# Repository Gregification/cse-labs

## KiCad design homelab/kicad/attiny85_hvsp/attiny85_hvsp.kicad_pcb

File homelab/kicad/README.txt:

sources & breif instructions for everything in the libraries folder
	clone the github / gitlab ones

https://github.com/Digi-Key/digikey-kicad-library
https://gitlab.com/kicad/libraries/kicad-symbols
https://gitlab.com/kicad/libraries/kicad-footprints

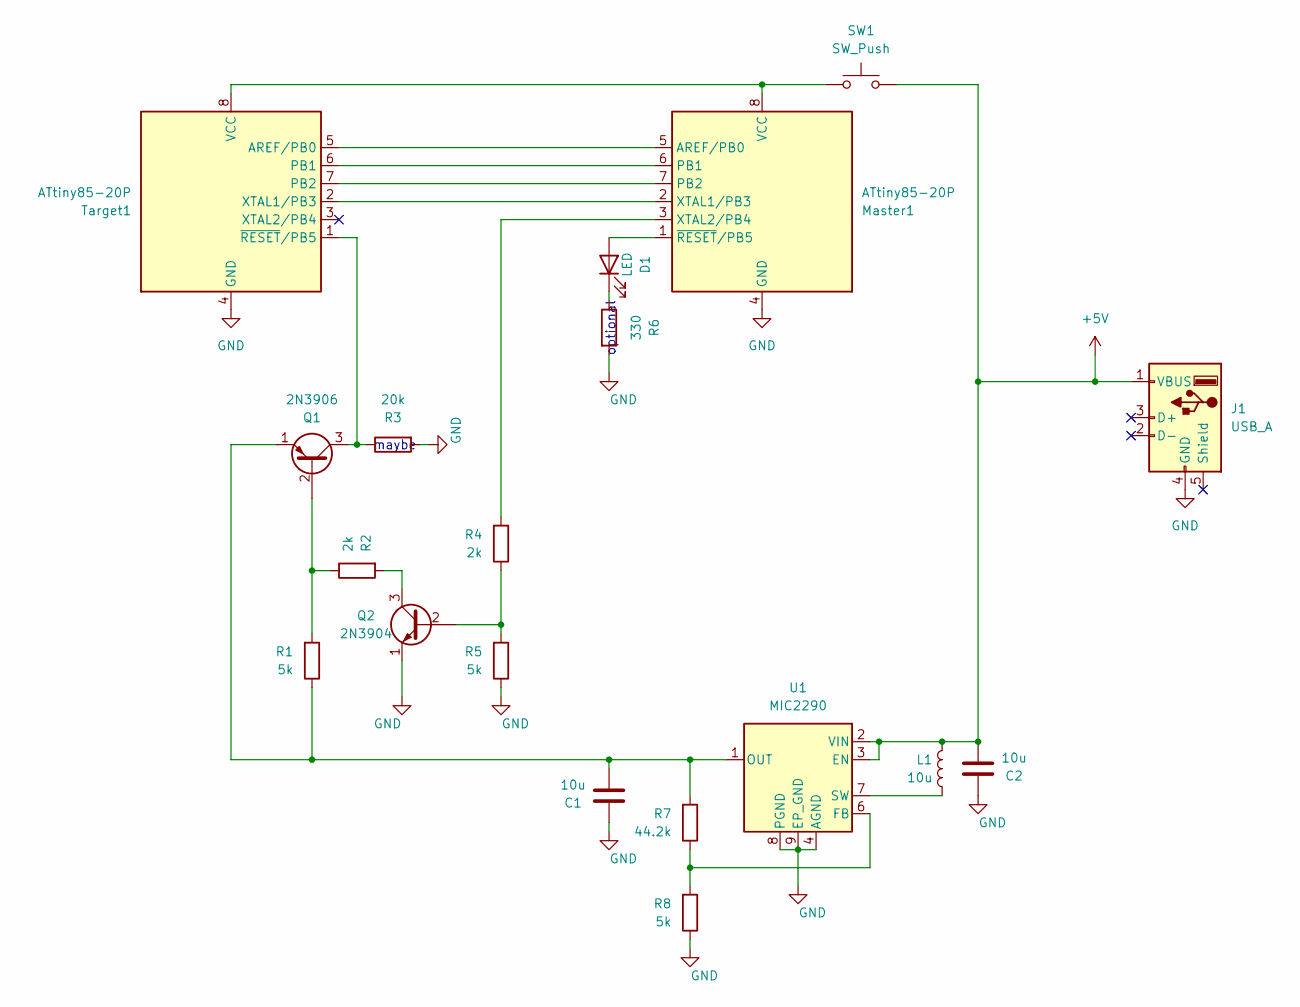
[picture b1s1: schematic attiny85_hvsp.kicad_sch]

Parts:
C1, C2: 10u; C_1210_3225Metric
D1: LED; LED_Rectangular_W3.0mm_H2.0mm
J1: USB_A; USB_A_Molex_48037-2200_Horizontal
L1: 10u; IDCP2218-01
Master1: ATtiny85-20P; DIP-8_W7.62mm
Q1: 2N3906; TO-92L_HandSolder
Q2: 2N3904; TO-92L_HandSolder
R1, R5, R8: 5k; R_0805_2012Metric
R2, R4: 2k; R_0603_1608Metric
R3: 20k; R_0805_2012Metric
R6: 330; R_2010_5025Metric
R7: 44.2k; R_1206_3216Metric
SW1: SW_Push; SW_SPST_Omron_B3FS-101xP
Target1: ATtiny85-20P; DIP-8_W7.62mm
U1: MIC2290; Micrel_MLF-8-1EP_2x2mm_P0.5mm_EP0.6x1.2mm

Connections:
+5V: C2.1, J1.1 (VBUS), L1.1, SW1.2, U1.2 (VIN), U1.3 (EN)
GND: C1.2, C2.2, J1.4 (GND), Master1.4 (GND), Q2.1 (E), R3.2, R5.1, R6.2, R8.1, Target1.4 (GND), U1.4 (AGND), U1.8 (PGND), U1.9 (EP_GND)
unnamed: D1.2 (A), Master1.1 (~RESET/PB5)
unnamed: D1.1 (K), R6.1
unnamed: Master1.5 (AREF/PB0), Target1.5 (AREF/PB0)
unnamed: Master1.6 (PB1), Target1.6 (PB1)
unnamed: Master1.7 (PB2), Target1.7 (PB2)
unnamed: Master1.8 (VCC), SW1.1, Target1.8 (VCC)
unnamed: Master1.2 (XTAL1/PB3), Target1.2 (XTAL1/PB3)
unnamed: Master1.3 (XTAL2/PB4), R4.2
unnamed: Q1.2 (B), R1.2, R2.1
unnamed: Q1.3 (C), R3.1, Target1.1 (~RESET/PB5)
unnamed: C1.1, Q1.1 (E), R1.1, R7.2, U1.1 (OUT)
unnamed: Q2.2 (B), R4.1, R5.2
unnamed: Q2.3 (C), R2.2
unnamed: R7.1, R8.2, U1.6 (FB)
unnamed: L1.2, U1.7 (SW)

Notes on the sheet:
maybe
optional

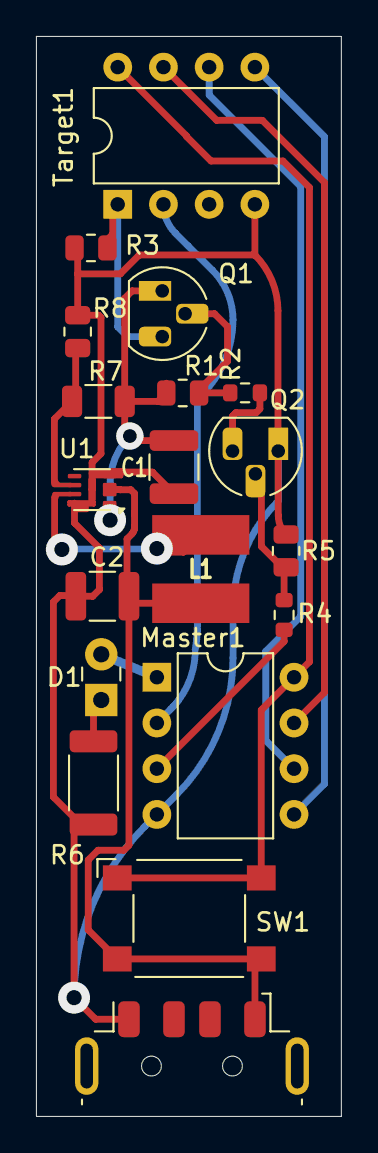
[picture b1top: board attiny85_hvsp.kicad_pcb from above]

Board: 2 copper layers, 16.9 x 60.0 mm, 19 parts (0 on the bottom side), 17 nets.

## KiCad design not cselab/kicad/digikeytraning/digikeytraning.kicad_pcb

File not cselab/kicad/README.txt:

sources & breif instructions for everything in the libraries folder
https://github.com/Digi-Key/digikey-kicad-library
	- add lib to libs folder. import from within kicad

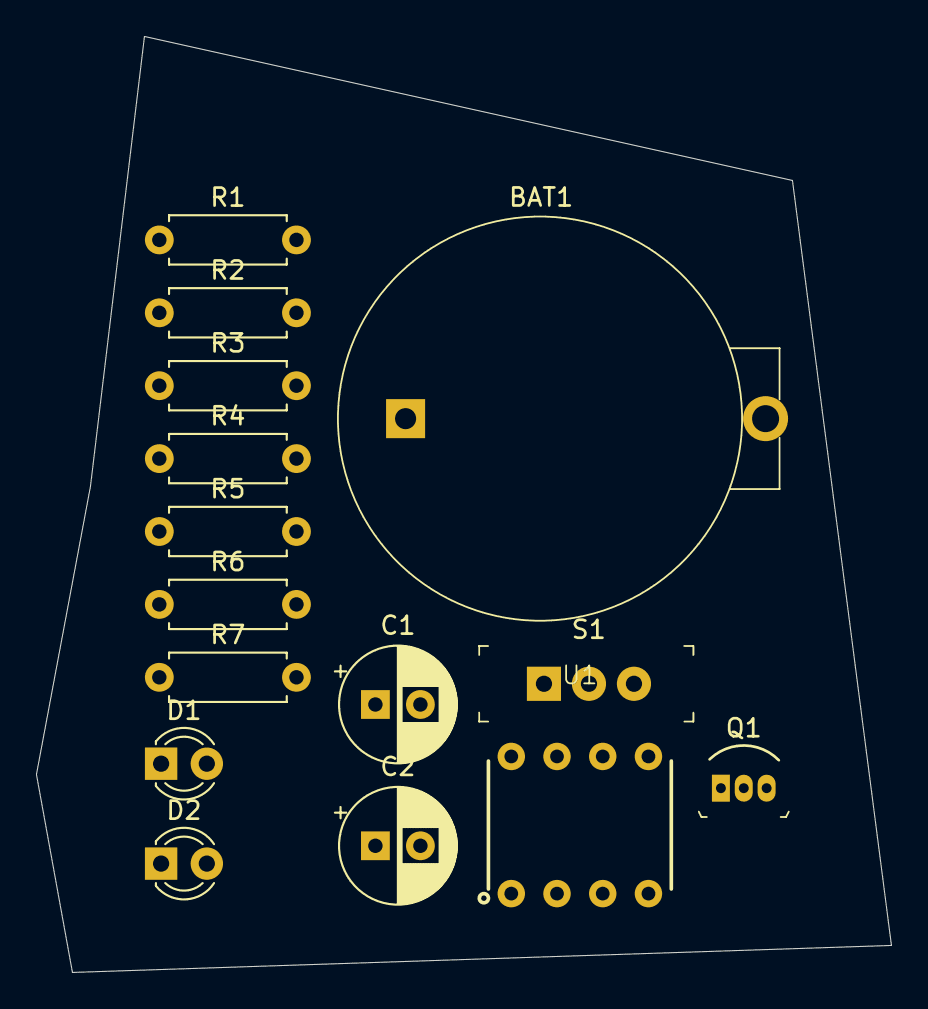
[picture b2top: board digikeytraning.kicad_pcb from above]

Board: 2 copper layers, 47.5 x 52.0 mm, 15 parts (0 on the bottom side), 11 nets, no tracks yet.

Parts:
BAT1: BS-7; Battery_Holder_Coin_2032_BS-7
C1: 10u; CP_Radial_D6.3mm_P2.50mm
C2: 100u; CP_Radial_D6.3mm_P2.50mm
D1, D2: LED RED; LED_D3.0mm
Q1: 2N3904; TO-92-3
R1, R3: 22k; R_Axial_DIN0207_L6.3mm_D2.5mm_P7.62mm_Horizontal
R2: 330k; R_Axial_DIN0207_L6.3mm_D2.5mm_P7.62mm_Horizontal
R4: 100k; R_Axial_DIN0207_L6.3mm_D2.5mm_P7.62mm_Horizontal
R5: 10k; R_Axial_DIN0207_L6.3mm_D2.5mm_P7.62mm_Horizontal
R6, R7: 100; R_Axial_DIN0207_L6.3mm_D2.5mm_P7.62mm_Horizontal
S1: EG1218; Switch_Slide_11.6x4mm_EG1218
U1: ICM7555-PDIP

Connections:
GND: BAT1.Neg, C1.2, C2.2, Q1.1 (E), R4.1, U1.1 (GND)
unnamed: BAT1.Pos, S1.3
unnamed: C2.1, R3.2, R4.2, R5.1
unnamed: D1.2 (A), R6.1
unnamed: D1.1 (K), D2.1 (K), Q1.3 (C)
unnamed: D2.2 (A), R7.1
unnamed: Q1.2 (B), R5.2
unnamed: R1.2, R2.1, U1.7 (DIS)
unnamed: R3.1, U1.3 (OUT)
unnamed: C1.1, R2.2, U1.2 (~TRIG), U1.6 (THRESH)
VCC: R1.1, R6.2, R7.2, S1.2, U1.4 (~RESET), U1.8 (Vdd)

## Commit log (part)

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2024-10-20 cse3320 : complete lab 2
2024-10-25 asdasd
2024-10-25 rebase 1
2024-10-25 more useable cli backup
2024-10-25 tests for lab 5
2024-10-25 cse3442 complete lab 5
2024-10-27 bck up
2024-10-27 complete lab 6
2024-10-27 complete lab 6, quartis change included
2024-10-28 eepy
2024-11-03 finalized 2 stage bjt v stepper. fet would have been better but gotta use these bjts for something
2024-11-03 missed a file
2024-11-03 maybe final pcb layout
2024-11-03 forgot ot push schematic
2024-11-03 complete lab7
2024-11-06 maybe milable hvsp pcb
2024-11-06 start of lab6
2024-11-08 removed teardrops and properly sized thermal reliefs
2024-11-11 complete C and R
2024-11-12 complete lab6
    forgot to push
2024-11-14 outline of funky fs
2024-11-14 working lab 3
2024-11-15 my first ever incomplete **** assignemtn ever and its because of jude !!!
    how tf is he allowed to do what he does...
2024-11-15 juuuuudeeee does not get to see this
2024-11-15 complete core of lab 8
    baselined off canvas modules as suggested
2024-11-17 maybe bantam safe layout
2024-11-17 bantam friendly layout
2024-11-20 hack job lab8
2024-11-21 athvsp
2024-11-25 corrected lab folder name
2024-11-25 bad spi thing, i hate the docs
2024-11-26 protoocl not working
2024-11-26 mouser has exact match
2024-11-26 exact match of footprint found
2024-11-29 term proj outline
2024-11-30 working display
2024-11-30 complete minimal ui. frmaework outline.
    added a working barrel shifter
    added a maybe working CLA
    added F32AS starting point
2024-12-01 who ever made the supplied pin assignments are evil
2024-12-01 working adder, buggy raw iput mode though
2024-12-01 working subtractor, however, signbit correct but not displaying
2024-12-01 complete subtractor
    bug: sign bit is set but display does not show it
    missing raw binary display
2024-12-02 tmp bck up
2024-12-02 complete lab7
    was done last week, forgot to push
2024-12-03 50/50 working lab7
2024-12-14 attiny to attiny was a terrible starting point
2024-12-14 working tiny85 high fuse resetter on TM4c123G
2025-01-05 git ignore hel
2025-01-06 XDS110 config mismatch with default CCS projects
    temp solution is to baseline off of generated Sysconfig projects ... might be intentionall from TI
2025-01-29 risc lab1
2025-02-03 risc lab2 instruction handling
2025-02-03 gitignore removes all but source files
2025-02-06 risscv
2025-02-06 corrected top, TODO new hardware to test. do later
2025-02-06 iot p1, outtline
2025-02-07 working reset
2025-02-08 cse4354 some omre work
2025-02-08 now able to compile to cortex-M4+ . yippie!
    all i did was add some extra compiler flags CCS wasent able to generate for some reason. see msp0l11306fiddle/notes folder for info
2025-02-08 16b hex display
2025-02-09 somewaht working tests
2025-02-10 cse4352 ex stage. most tests implimented, passing all
2025-02-10 bkup
2025-02-12 back up
2025-02-12 is37 stuff
2025-02-14 lab2 thing
2025-02-16 corrected missinf IRQ vector
2025-02-16 10 mcp0l1306 for the price of 1 tm4c
2025-02-17 complete os lab 1
2025-02-19 ip checksum offset issue
2025-02-19 untested complete lab3
2025-02-19 complete lab 3
2025-02-20 working ip and tcp tx checksums
2025-02-20 maybe working tcp rx istcp
2025-02-24 untested arp and tcp setup
2025-02-24 untested backup
2025-02-24 why cant we use cpp :(
2025-02-26 corrected timeout handler
2025-02-27 removed client sent keep alive. now failing during closing
2025-02-27 ported over mqtt config from laptop, now actually works
2025-02-28 mqtt outline
2025-02-28 maybne working
2025-03-01 more failed debugging ...
2025-03-01 malloc problems
2025-03-02 outlie lab 4
2025-03-02 untested. synth success
2025-03-05 behind in in risk
2025-03-08 working memory access
    git ignore is not doing what i need :(
2025-03-08 complete lab 4
2025-03-09 rearranged tcp state machine, works slightly better
2025-03-09 gitignore directory regex once again failing me
2025-03-09 sm details still crapped out
2025-03-10 corrected string termination bug
2025-03-11 qol improvements, also slightly more stable :)
2025-03-11 removed dynamic memory code, worse design but it works
    unable to determine why mem allocatating fails
2025-03-12 slap job mqtt outline
2025-03-12 mqtt publish working
2025-03-12 working sub abd unsub
2025-03-12 corrected connection issue source in mqtt broker config
2025-03-13 cleaned up, investigating fcl thingggy
2025-03-14 complete project 1, incomplete testing
2025-03-14 msp som progres
2025-03-15 duplicate msg problem
2025-03-16 apparently this crashes in debug mode
2025-03-16 git exploding
2025-03-16 tcp remade for hte 100th time
    gitignore braeking down magically
2025-03-16 complete mqtt core
2025-03-16 commented out ping control, wasent workign out
2025-03-16 msp0l uart tx working
2025-03-17 flushed out test cases for lab 4
2025-03-18 complete iot
    demoed to leo on 3/18/2025
2025-03-18 corrected uart rx error
    aaaaahhhhhhhhhhhhhhh should have caught htis immideatly but noo
2025-03-19 maybe working spi
2025-03-20 more git troubles
    pc and iw shiffling though pipeline
2025-03-20 mostly complete lab5, needs ILA setup for confirmation
2025-03-21 working basic pipeline
2025-03-22 all but e break
2025-03-22 complete lab5
2025-03-22 updated adc dumper
2025-03-24 sysconfig dosent allow for h files on windos
2025-03-24 ebreak logiclogic slightly modified
2025-03-24 adc somewhat works on reboot
2025-03-25 reolved one shot problem with ACD
2025-03-25 figured out spi
2025-03-27 unable to use more than 4 adcs "
2025-03-27 lab6 rearranged pipeline
2025-03-27 corrected pipeline buffers
    determined and noted how DLADC12 register priority is set up
2025-03-27 bkup\
2025-03-27 10channel v sensor
2025-03-28 working dataforwarding
2025-03-28 msp0m1306 incomplete symbol
2025-03-28 complete lab6
2025-03-29 outline
2025-03-30 lightling near by, my puter may explode
2025-03-31 consider using addresses anyways, the dam thing wont transmitt
2025-04-01 leo is goat
2025-04-02 me is behind :(
2025-04-02 failling to receive
2025-04-03 1 bit transfer
2025-04-03 its not transmitting apparently
2025-04-03 lcknealcken
2025-04-05 seemingly working
2025-04-05 lab7
2025-04-07 confimed msp spi
2025-04-08 trimmed
2025-04-08 lab8 prep
2025-04-08 im going to lose it lose it
2025-04-08 corrected spi transfer
2025-04-09 tx/rx then swap roles and it works
2025-04-09 found out why my lab 7 was working so well
2025-04-09 finiky receiver
2025-04-09 everything stopped working
2025-04-10 still no work
2025-04-11 toggle roles, and it wokrs, maybe
2025-04-11 git lieing
2025-04-11 mildly ocnsistent rx
2025-04-11 mbic the datasheet is evil, do not follow its steps in order for it to work
2025-04-11 maybe working timer
2025-04-11 alcejnclkc
2025-04-12 stuff getting across
2025-04-12 changed rx
2025-04-13 working client sync
2025-04-15 removed redundant types
2025-04-16 hlkeclnkaclnkaeclnkaclekcg
2025-04-17 apparently df never worked???
2025-04-17 aekcbajec
2025-04-17 tuned up iot
2025-04-17 good er nuff
2025-04-17 claenc
2025-04-18 aceljaebc
2025-04-18 integration seemingly working
2025-04-18 aeclekcn
2025-04-18 aecklcankcaenk
2025-04-18 working auto
2025-04-19 good e nuff
2025-04-19 lab7 destroyed it all :(
2025-04-19 project 2 all functions
2025-04-19 kcaeskbhlaseckbhac
2025-04-20 lab7 back in buisness
2025-04-20 aecaec
2025-04-20 brute force dft/idft implimentation
2025-04-20 holy molie lab8 recovered partial
2025-04-21 why :9
2025-04-22 brutea force
2025-04-22 addressing problem
2025-04-22 ecanklecanklecalnkaeclnkaec
2025-04-23 working mem load
2025-04-23 maybe complete lab8
2025-04-23 blinker
2025-04-23 o;;/
2025-04-25 topic parse working
2025-04-26 hate
2025-04-26 complete frameowrk, missing some packets
2025-04-26 lab 8 project getting resused for lab9
2025-04-26 eacjnaecnlaec
2025-04-27 mklac
2025-04-27 complete load after write stalling
2025-04-27 working lab 9
2025-04-27 final lab 9
2025-04-29 corrected mqtt tpoic name
2025-04-29 working door team
2025-04-29 working weather team
2025-04-29 updated door team
2025-04-29 termela team happy
2025-04-29 updated weather pressure thing
2025-05-06 signals final project
2025-05-07 project setup
2025-05-07 proj2
2025-05-09 compiler updated itself and seems to acutall compile things now
2025-05-10 holy molie css just wiped a file off teh face of the drive
2025-05-11 bippie
2025-05-27 mspm0l freertos slap together
2025-05-27 bad imports
2025-08-24 asdas
2025-08-25 all but reboot
2025-08-29 qol changes
2025-09-04 thingy ma jig
2025-09-04 laeclkaecnaec
2025-09-06 mini project registers make me sad
2025-09-09 lab 1 complete
2025-09-11 irq moment
2025-09-11 mini project some work
2025-09-12 irq hel
2025-09-12 pendsv pending destruction
    cant get it or MPU handlers to trigger. probably missing some reg somewhere
2025-09-14 inconsistently triggering
    pendSV triggering all of a sudden. could have swore I ran the exact same code like 5 mins before and it didnt trigger???
2025-09-14 faults on demand
2025-09-16 re-figured out pwm
2025-09-16 lkzdz
2025-09-16 sdfdsffd
2025-09-16 aejea
2025-09-16 cuskaskbjlsbascjkl
2025-09-17 bluh
2025-09-19 malloc allocaiton being sad
2025-09-22 probably working flash access
    code executes but the default rule should be +ALL but its not able to do mem io
2025-09-22 MPU sub region addressees being funky
    offset by 0x20000000, the SRAM offset, so the SRAM ones are effectively covering FLASH :(. looks like something with how the regions length is stored
2025-09-23 lnecalnaelnecalnecanklceakcadkcakac
2025-09-23 mostly working micro lab
2025-09-23 aelcknae
2025-09-23 sdfd
2025-09-23 afasd
2025-09-23 alkn
2025-09-23 complete lab2 ( :( )
2025-09-23 where tf os pe0
2025-09-24 added cheesy register dump confirmation
2025-09-24 multi alloc test cases
2025-09-24 lnkaeclnca
2025-09-24 lsaljaceaclk
2025-09-25 buttoned up
2025-09-25 500khb can
2025-09-30 what we have rn lab3
2025-09-30 adc losh
2025-09-30 adsf
2025-09-30 lab 3 complete
2025-10-07 5 button inputs in a row
2025-10-14 lab4 baseline
2025-10-14 lookup table
2025-10-14 bad wiring or something??
2025-10-17 ddsffs
2025-10-19 forgot red board. cant test
2025-10-21 sleep func kills sys tick bug
    idk why that happens. worst case memory layout is cooked
2025-10-24 semi working thing
2025-10-25 pendsv maybe working. off byy 1 somewhere ?
2025-10-26 uuuuuuoooooohhhhhhh yippie
    MSP was stealth decrementing between when pendSV isr triggered and the pendSV handler running.
2025-10-26 sys tick cleaner. still exits on sleep though
    setting the state though the sleep function causes sys tick to stop triggering? registers still show the counter going and isrs enabledbut it just dosnet run
2025-10-26 input edge timing not quote there
2025-10-28 complete lab 5
2025-10-30 maybe sleep
2025-10-30 yippers!
2025-10-30 kaclnca
2025-10-31 notes
2025-10-31 corrected systick speed
2025-10-31 block maybe
2025-11-01 maybe lock unlock
2025-11-04 me when
2025-11-04 asdll
2025-11-04 ai stuff
2025-11-04 lknas
2025-11-04 working locks
2025-11-05 incomeplete step 13
2025-11-09 wokring scheduler
2025-11-10 working V2C and C2V
2025-11-10 magic number adjustment
2025-11-10 comments
2025-11-11 meow meow
2025-11-14 priority scheduler & pendSv adjustment
    shuffled the fake stack stuff over to pendSV
2025-11-15 removed lower stack MPU allowance default
2025-11-15 software fix for btn 0
2025-11-15 windows crashing :(
2025-11-15 theyre forcing me to write assembly D:
2025-11-18 good er nuff PS
2025-11-18 global sram mask for current task
2025-11-18 lab 8 start
2025-11-18 working scan
2025-11-19 pidof
2025-11-20 kill resume
2025-11-20 critter command
2025-11-25 complete lab 8
2025-11-25 hhhh
2025-11-25 complete lab 7
2025-11-28 svic register leak fixed. stoped createThread ram access from changing
    meow meow
2025-12-02 andrew approved rtos thingy
2025-12-02 fixed pc7
    board issue. replaced the board
2026-01-28 lab 1 complete
    I LOVE DOG WATER IDES !!!! ITS GOING O BE A IED!!
2026-02-13 lub too
2026-02-13 lub2
2026-02-21 womp womp
2026-02-21 stepper steps. yippie
2026-02-21 a bit faster
2026-03-06 i lub lub tree weee
    this sucks
2026-03-06 demoed lub tre
2026-03-23 working spi
2026-03-25 lab4 complete
2026-03-28 piddle maxxing
2026-04-06 lnncslnkaeclnkseclnksc
2026-04-08 seems to work
